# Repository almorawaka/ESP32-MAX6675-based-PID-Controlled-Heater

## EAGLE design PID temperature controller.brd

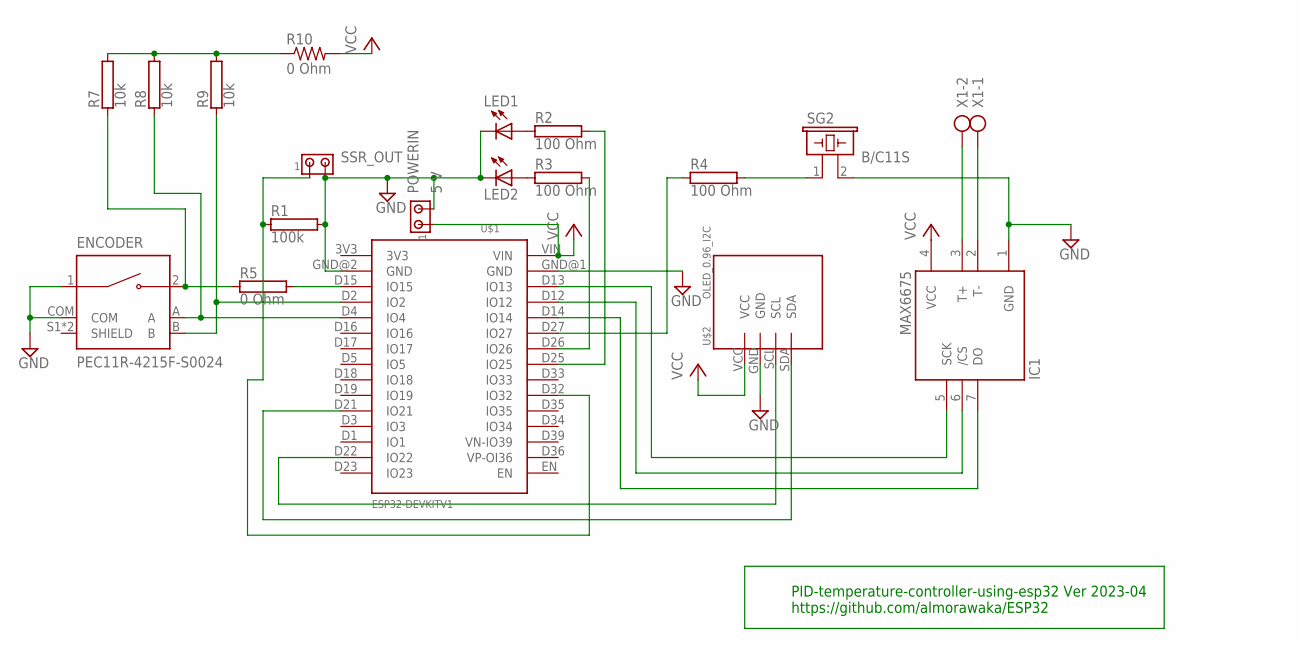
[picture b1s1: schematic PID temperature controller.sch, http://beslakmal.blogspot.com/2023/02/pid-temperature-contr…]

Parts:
ENCODER: PEC11R-4215F-S0024; XDCR_PEC11R-4215F-S0024
IC1: MAX6675; SO08
LED1, LED2: LED3MM
POWERIN: 5 V; 10X02MTA
R1: 100k; RS1/8
R2, R3, R4: 100 Ohm; RS1/8
R5: 0 Ohm; RS1/8
R7, R8, R9: 10k; RS1/8
R10: 0 Ohm; 0207/12
SG2: B/C11S
SSR_OUT: MTA02-100; 10X02MTA
U$1: ESP32DEVKITV1; ESP32-DEVKITV1
U$2: OLED_0.96_I2C
X1: AK300/2

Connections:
GND: ENCODER.1, ENCODER.COM, IC1.1 (GND), LED1.K (C), LED2.K (C), POWERIN.2, R1.2, SG2.2, SSR_OUT.2, U$1.GND@1 (GND), U$1.GND@2 (GND), U$2.GND
unnamed: IC1.7 (DO), U$1.D14 (IO14)
unnamed: IC1.6 (/CS), U$1.D12 (IO12)
unnamed: IC1.5 (SCK), U$1.D13 (IO13)
unnamed: R4.1, U$1.D27 (IO27)
unnamed: IC1.3 (T+), X1.2
unnamed: IC1.2 (T-), X1.1
unnamed: U$1.D21 (IO21), U$2.SDA
unnamed: U$1.D22 (IO22), U$2.SCL
unnamed: R1.1, SSR_OUT.1, U$1.D32 (IO32)
unnamed: ENCODER.2, R5.1, R7.1
unnamed: R5.2, U$1.D15 (IO15)
unnamed: LED1.A, R2.1
unnamed: LED2.A, R3.1
unnamed: R3.2, U$1.D26 (IO26)
unnamed: R2.2, U$1.D25 (IO25)
unnamed: R4.2, SG2.1
unnamed: R7.2, R8.2, R9.2, R10.1
unnamed: ENCODER.B, R9.1, U$1.D2 (IO2)
unnamed: ENCODER.A, R8.1, U$1.D4 (IO4)
VCC: IC1.4 (VCC), POWERIN.1, R10.2, U$1.VIN, U$2.VCC

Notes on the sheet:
PID-temperature-controller-using-esp32 Ver 2023-04 https://github.com/almorawaka/ESP32

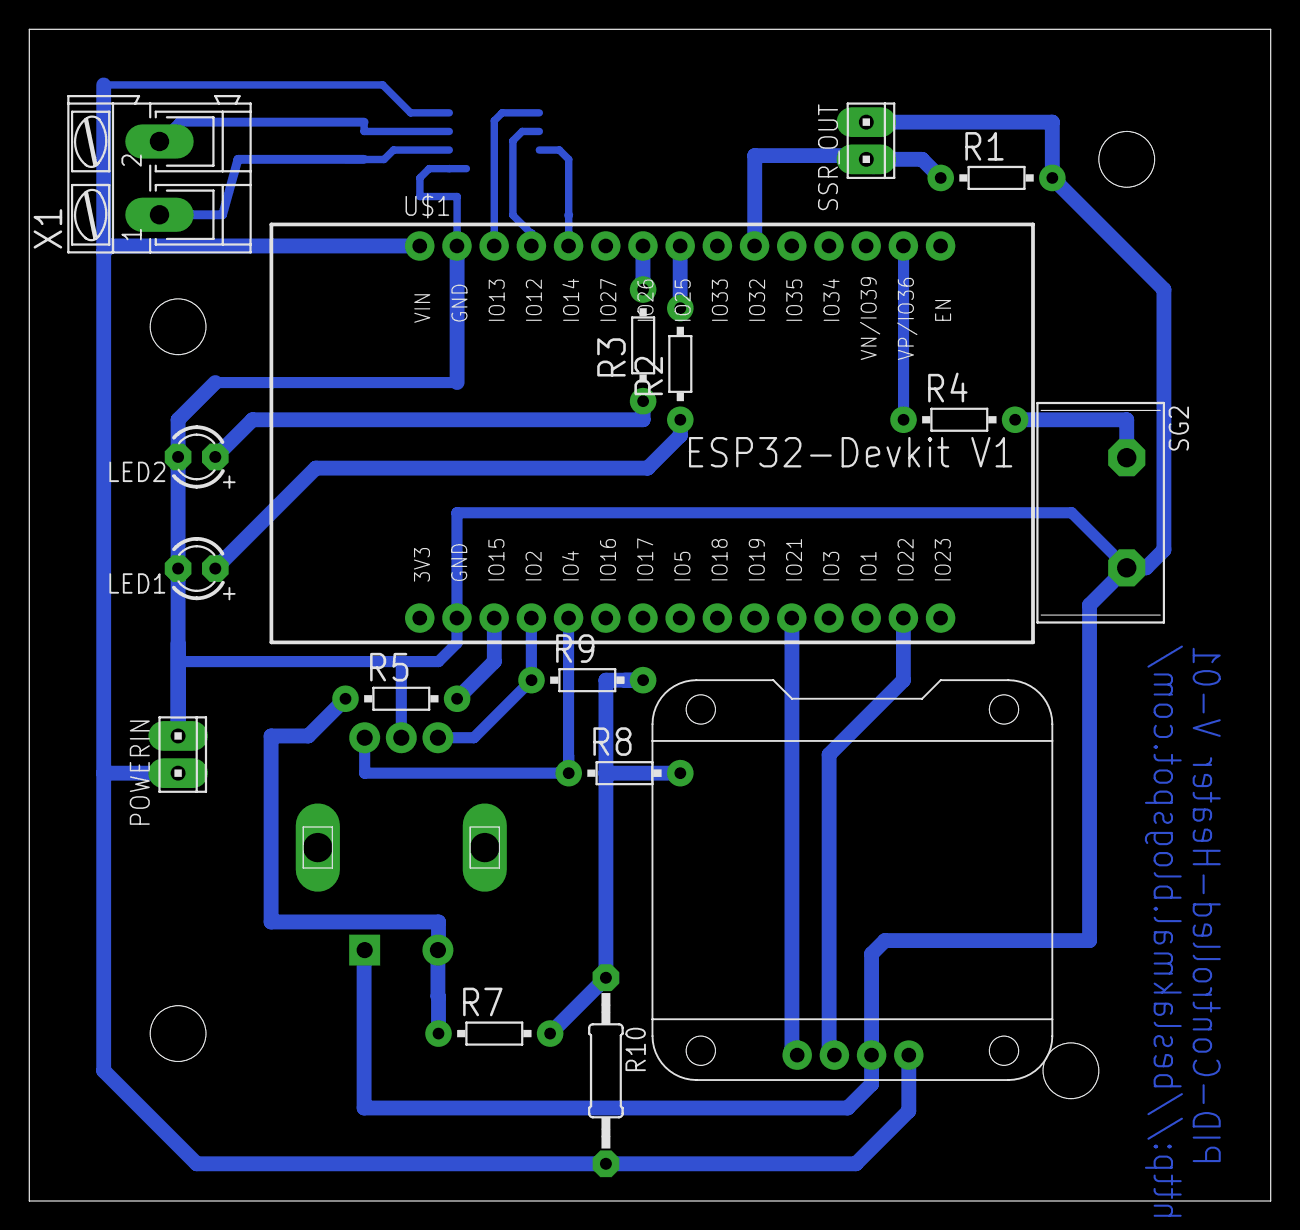
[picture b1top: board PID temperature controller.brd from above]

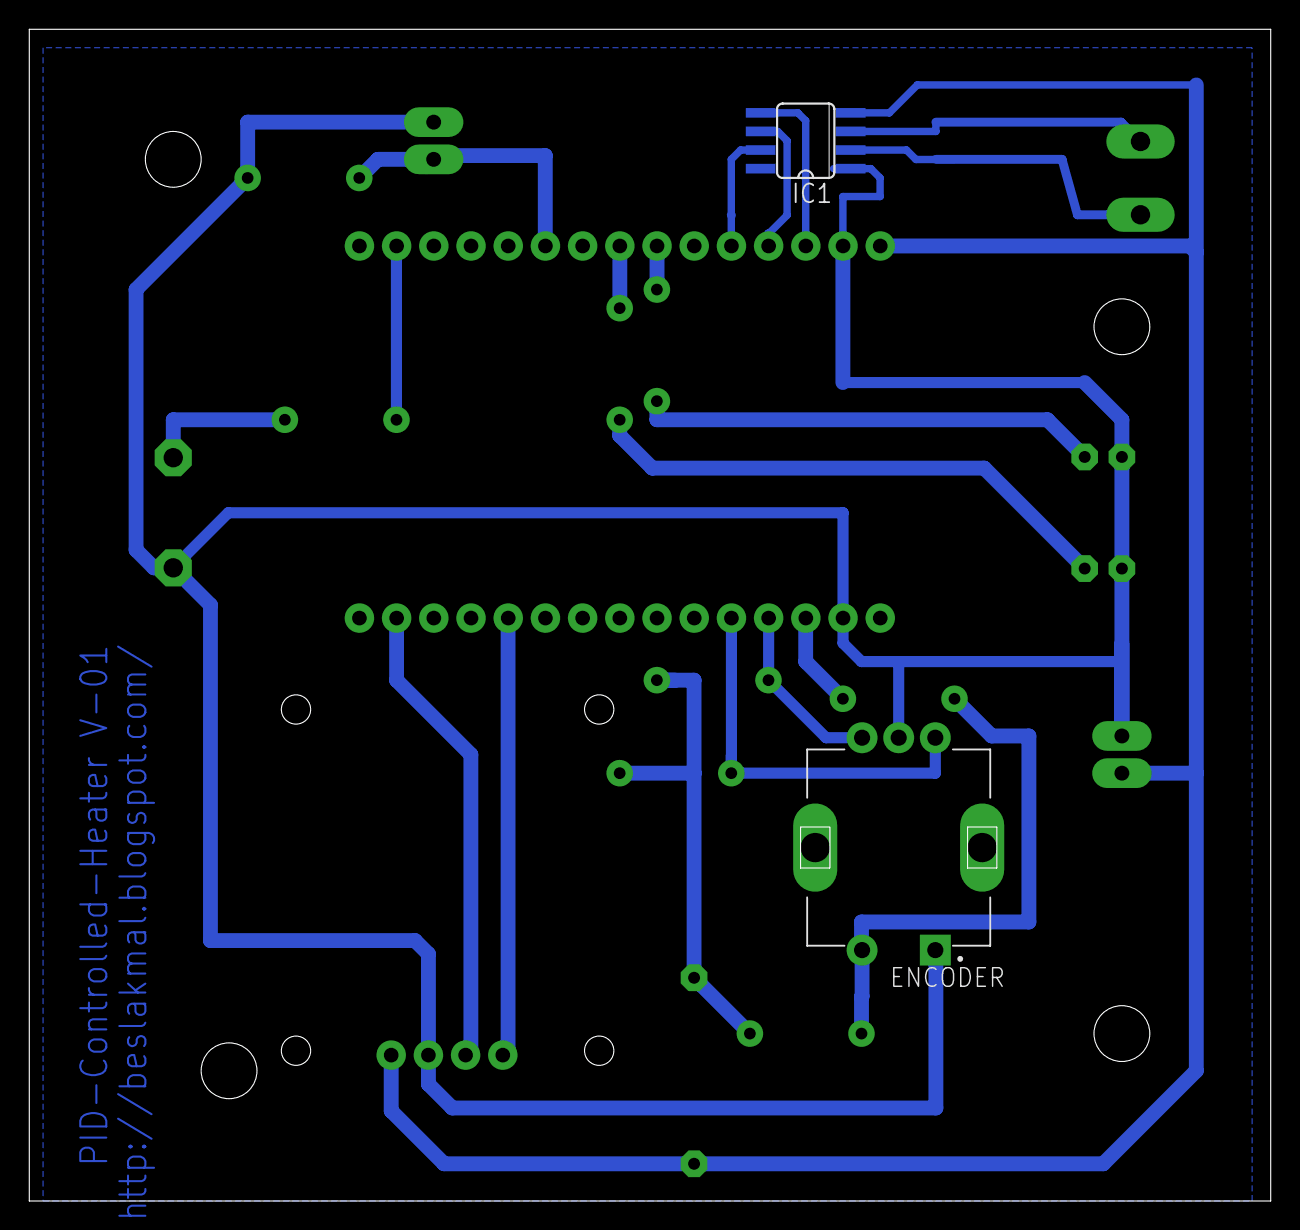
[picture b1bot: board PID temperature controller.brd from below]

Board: 2 copper layers, 84.8 x 80.0 mm, 19 parts (2 on the bottom side), 21 nets.

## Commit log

2023-01-23 buzzer, stausLED
    buzzer to generate startup tone, temperature alternation tones, etc. Two LEDs ready(GREEN) notReady (RED) adds to recognize the temperature if not in the range
2023-01-23 same code with web -OTA
    Dialog 4G, sema9454
2023-01-23 required libraries
2023-02-05 Eagle CAD file added
2023-02-20 Eagle Schematic and Brd file added
    Eagle Schematic and Brd file added
2023-02-20 Update PID-Controller-ESP32-OTA.ino
    First Revision to best-fit PCB V-01
2023-02-20 PCB V-01
    Change GPIO to match with PCB V-01
